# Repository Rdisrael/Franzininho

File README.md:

This project still in development and many changes will be added to the projects

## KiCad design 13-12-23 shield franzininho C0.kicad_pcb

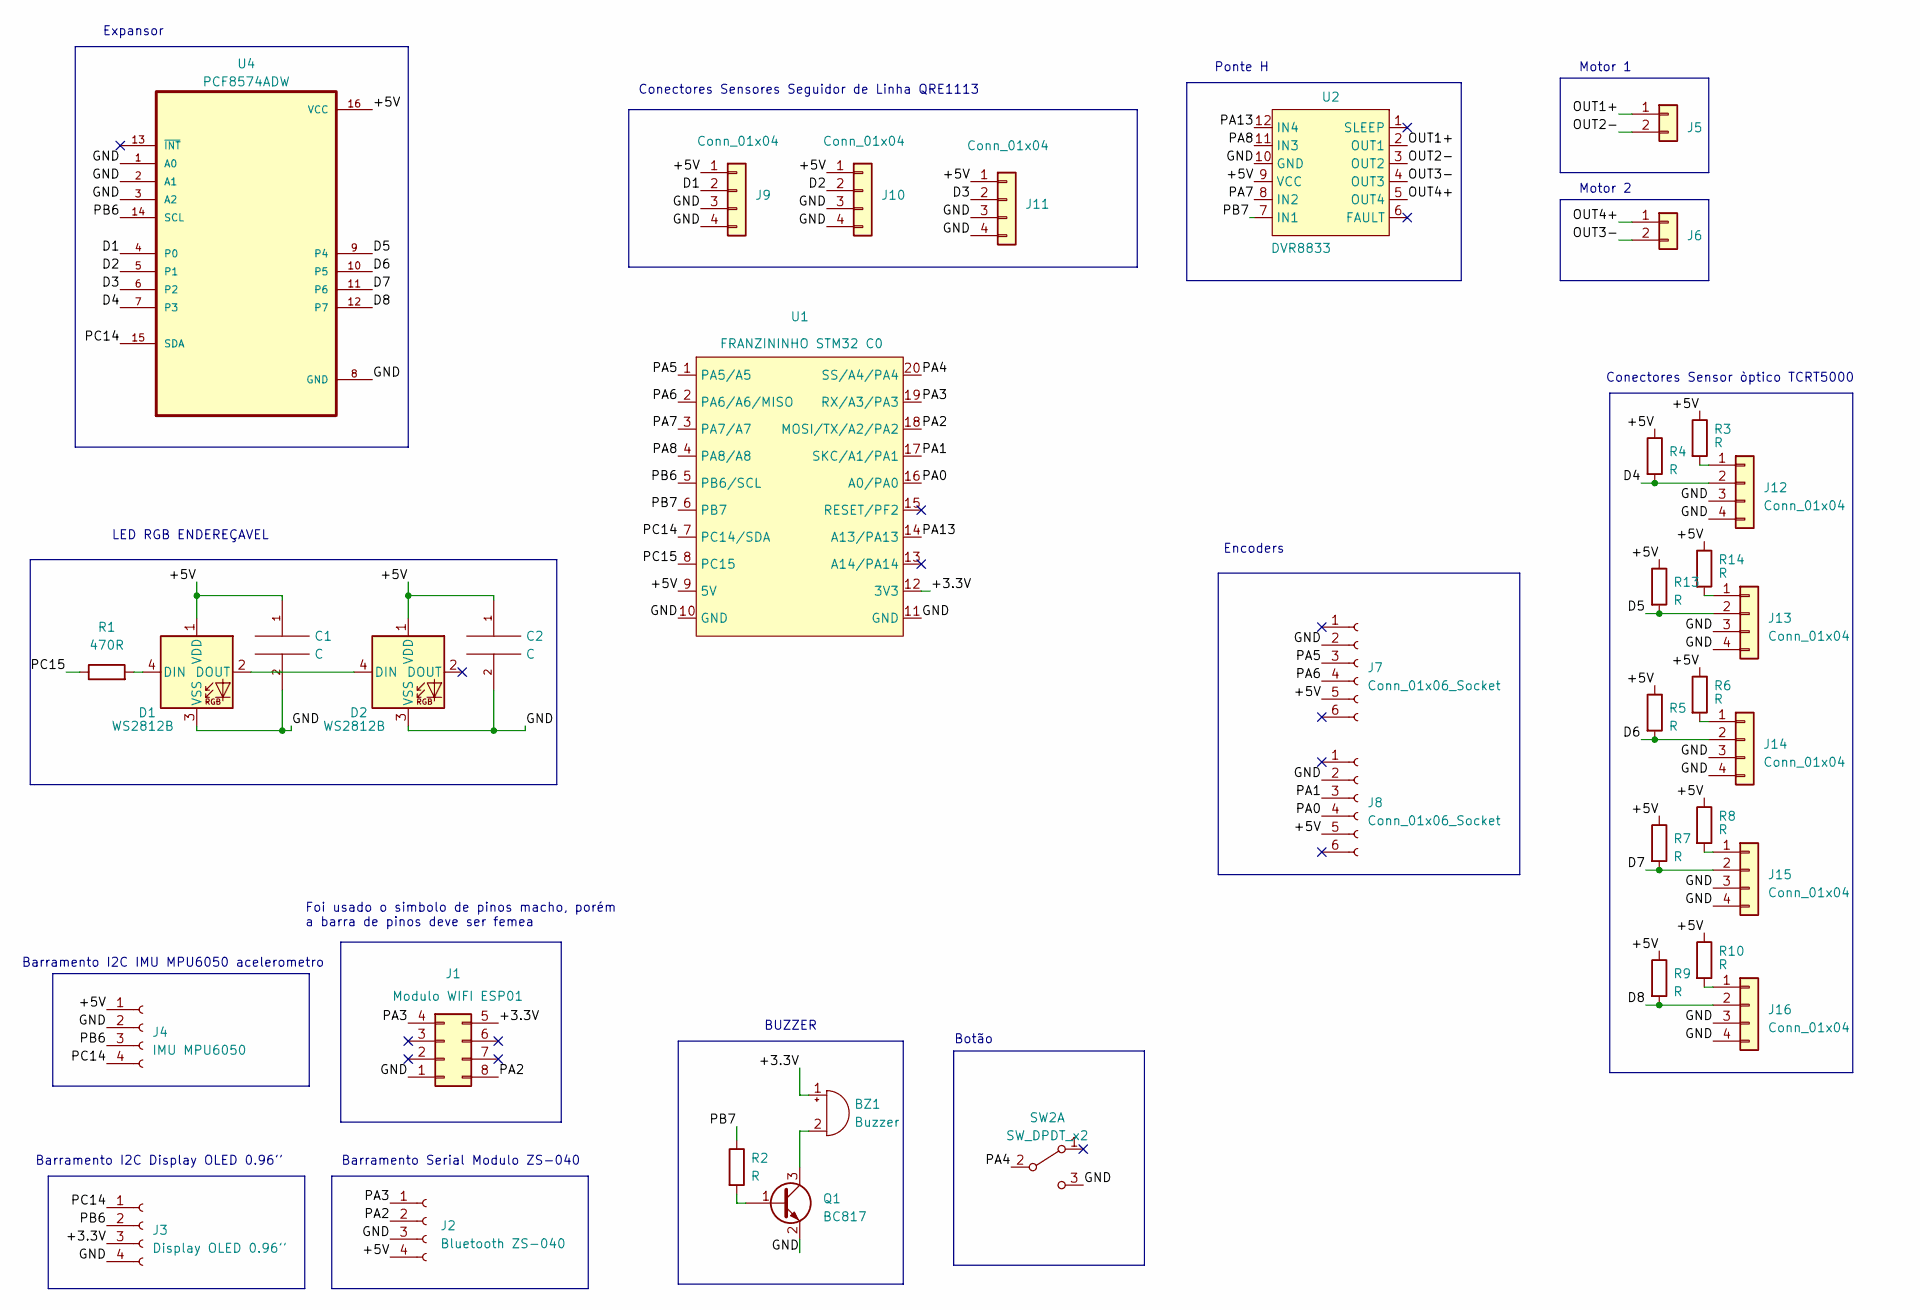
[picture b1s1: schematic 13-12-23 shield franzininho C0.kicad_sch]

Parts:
BZ1: Buzzer; Buzzer_12x9.5RM7.6
C1, C2: C; C_0805_2012Metric
D1, D2: WS2812B; LED_WS2812B_PLCC4_5.0x5.0mm_P3.2mm
J1: Modulo WIFI ESP01; PinSocket_2x04_P2.54mm_Vertical
J2: Bluetooth ZS-040; PinSocket_1x04_P2.54mm_Vertical
J3: Display OLED 0.96''; PinSocket_1x04_P2.54mm_Vertical
J4: IMU MPU6050; PinSocket_1x04_P2.54mm_Vertical
J5, J6: Screw_Terminal_01x02; Molex_KK-254_AE-6410-02A_1x02_P2.54mm_Vertical
J7, J8: Conn_01x06_Socket; PinSocket_1x06_P2.54mm_Vertical
J9, J10, J11, J12, J13, J14, J15, J16: Conn_01x04; Molex_KK-254_AE-6410-04A_1x04_P2.54mm_Vertical
Q1: BC817; SOT-23
R1: 470R; R_1206_3216Metric
R2, R3, R4, R5, R6, R7, R8, R9, R10, R13, R14: R; R_1206_3216Metric
SW2: SW_DPDT_x2; SW_CuK_JS202011CQN_DPDT_Straight
U1: FRANZININHO STM32 C0; Franzininho
U2: DVR8833; DRV8833 MODULE
U4: PCF8574ADW; SOIC127P1030X265-16N

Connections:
/+3.3V: BZ1.1 (-), J1.5, J3.3, U1.12 (3V3)
/+5V: C1.1, C2.1, D1.1 (VDD), D2.1 (VDD), J2.4, J4.1, J7.5, J8.5, J9.1, J10.1, J11.1, R3.1, R4.1, R5.1, R6.1, R7.1, R8.1, R9.1, R10.1, R13.1, R14.1, U1.9 (5V), U2.9 (VCC), U4.16 (VCC)
/D1: J9.2, U4.4 (P0)
/D2: J10.2, U4.5 (P1)
/D3: J11.2, U4.6 (P2)
/D4: J12.2, R4.2, U4.7 (P3)
/D5: J13.2, R13.2, U4.9 (P4)
/D6: J14.2, R5.2, U4.10 (P5)
/D7: J15.2, R7.2, U4.11 (P6)
/D8: J16.2, R9.2, U4.12 (P7)
/GND: C1.2, C2.2, D1.3 (VSS), D2.3 (VSS), J1.1, J2.3, J3.4, J4.2, J7.2, J8.2, J9.3, J9.4, J10.3, J10.4, J11.3, J11.4, J12.3, J12.4, J13.3, J13.4, J14.3, J14.4, J15.3, J15.4, J16.3, J16.4, Q1.2 (E), SW2.3 (C), U1.10 (GND), U1.11 (GND), U2.10 (GND), U4.1 (A0), U4.2 (A1), U4.3 (A2), U4.8 (GND)
/OUT1+: J5.1, U2.2 (OUT1)
/OUT2-: J5.2, U2.3 (OUT2)
/OUT3-: J6.2, U2.4 (OUT3)
/OUT4+: J6.1, U2.5 (OUT4)
/PA0: J8.4, U1.16 (A0/PA0)
/PA1: J8.3, U1.17 (SKC/A1/PA1)
/PA2: J1.8, J2.2, U1.18 (MOSI/TX/A2/PA2)
/PA3: J1.4, J2.1, U1.19 (RX/A3/PA3)
/PA4: SW2.2 (B), U1.20 (SS/A4/PA4)
/PA5: J7.3, U1.1 (PA5/A5)
/PA6: J7.4, U1.2 (PA6/A6/MISO)
/PA7: U1.3 (PA7/A7), U2.8 (IN2)
/PA8: U1.4 (PA8/A8), U2.11 (IN3)
/PA13: U1.14 (A13/PA13), U2.12 (IN4)
/PB6: J3.2, J4.3, U1.5 (PB6/SCL), U4.14 (SCL)
/PB7: R2.1, U1.6 (PB7), U2.7 (IN1)
/PC14: J3.1, J4.4, U1.7 (PC14/SDA), U4.15 (SDA)
/PC15: R1.1, U1.8 (PC15)
unnamed: BZ1.2 (+), Q1.3 (C)
unnamed: D1.4 (DIN), R1.2
unnamed: D1.2 (DOUT), D2.4 (DIN)
unnamed: J12.1, R3.2
unnamed: J13.1, R14.2
unnamed: J14.1, R6.2
unnamed: J15.1, R8.2
unnamed: J16.1, R10.2
unnamed: Q1.1 (B), R2.2

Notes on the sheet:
Ponte H
Barramento Serial Modulo ZS-040
Motor 2
Barramento I2C IMU MPU6050 acelerometro
Motor 1
Conectores Sensores Seguidor de Linha QRE1113
Barramento I2C Display OLED 0.96''
Encoders
Expansor
Conectores Sensor òptico TCRT5000
Botão
LED RGB ENDEREÇAVEL
Foi usado o simbolo de pinos macho, porém a barra de pinos deve ser femea
BUZZER

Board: 2 copper layers, 38 parts (3 on the bottom side), 38 nets, no tracks yet.

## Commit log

2024-01-26 adicionando primeiro layout do robo
2024-02-06 README.md
